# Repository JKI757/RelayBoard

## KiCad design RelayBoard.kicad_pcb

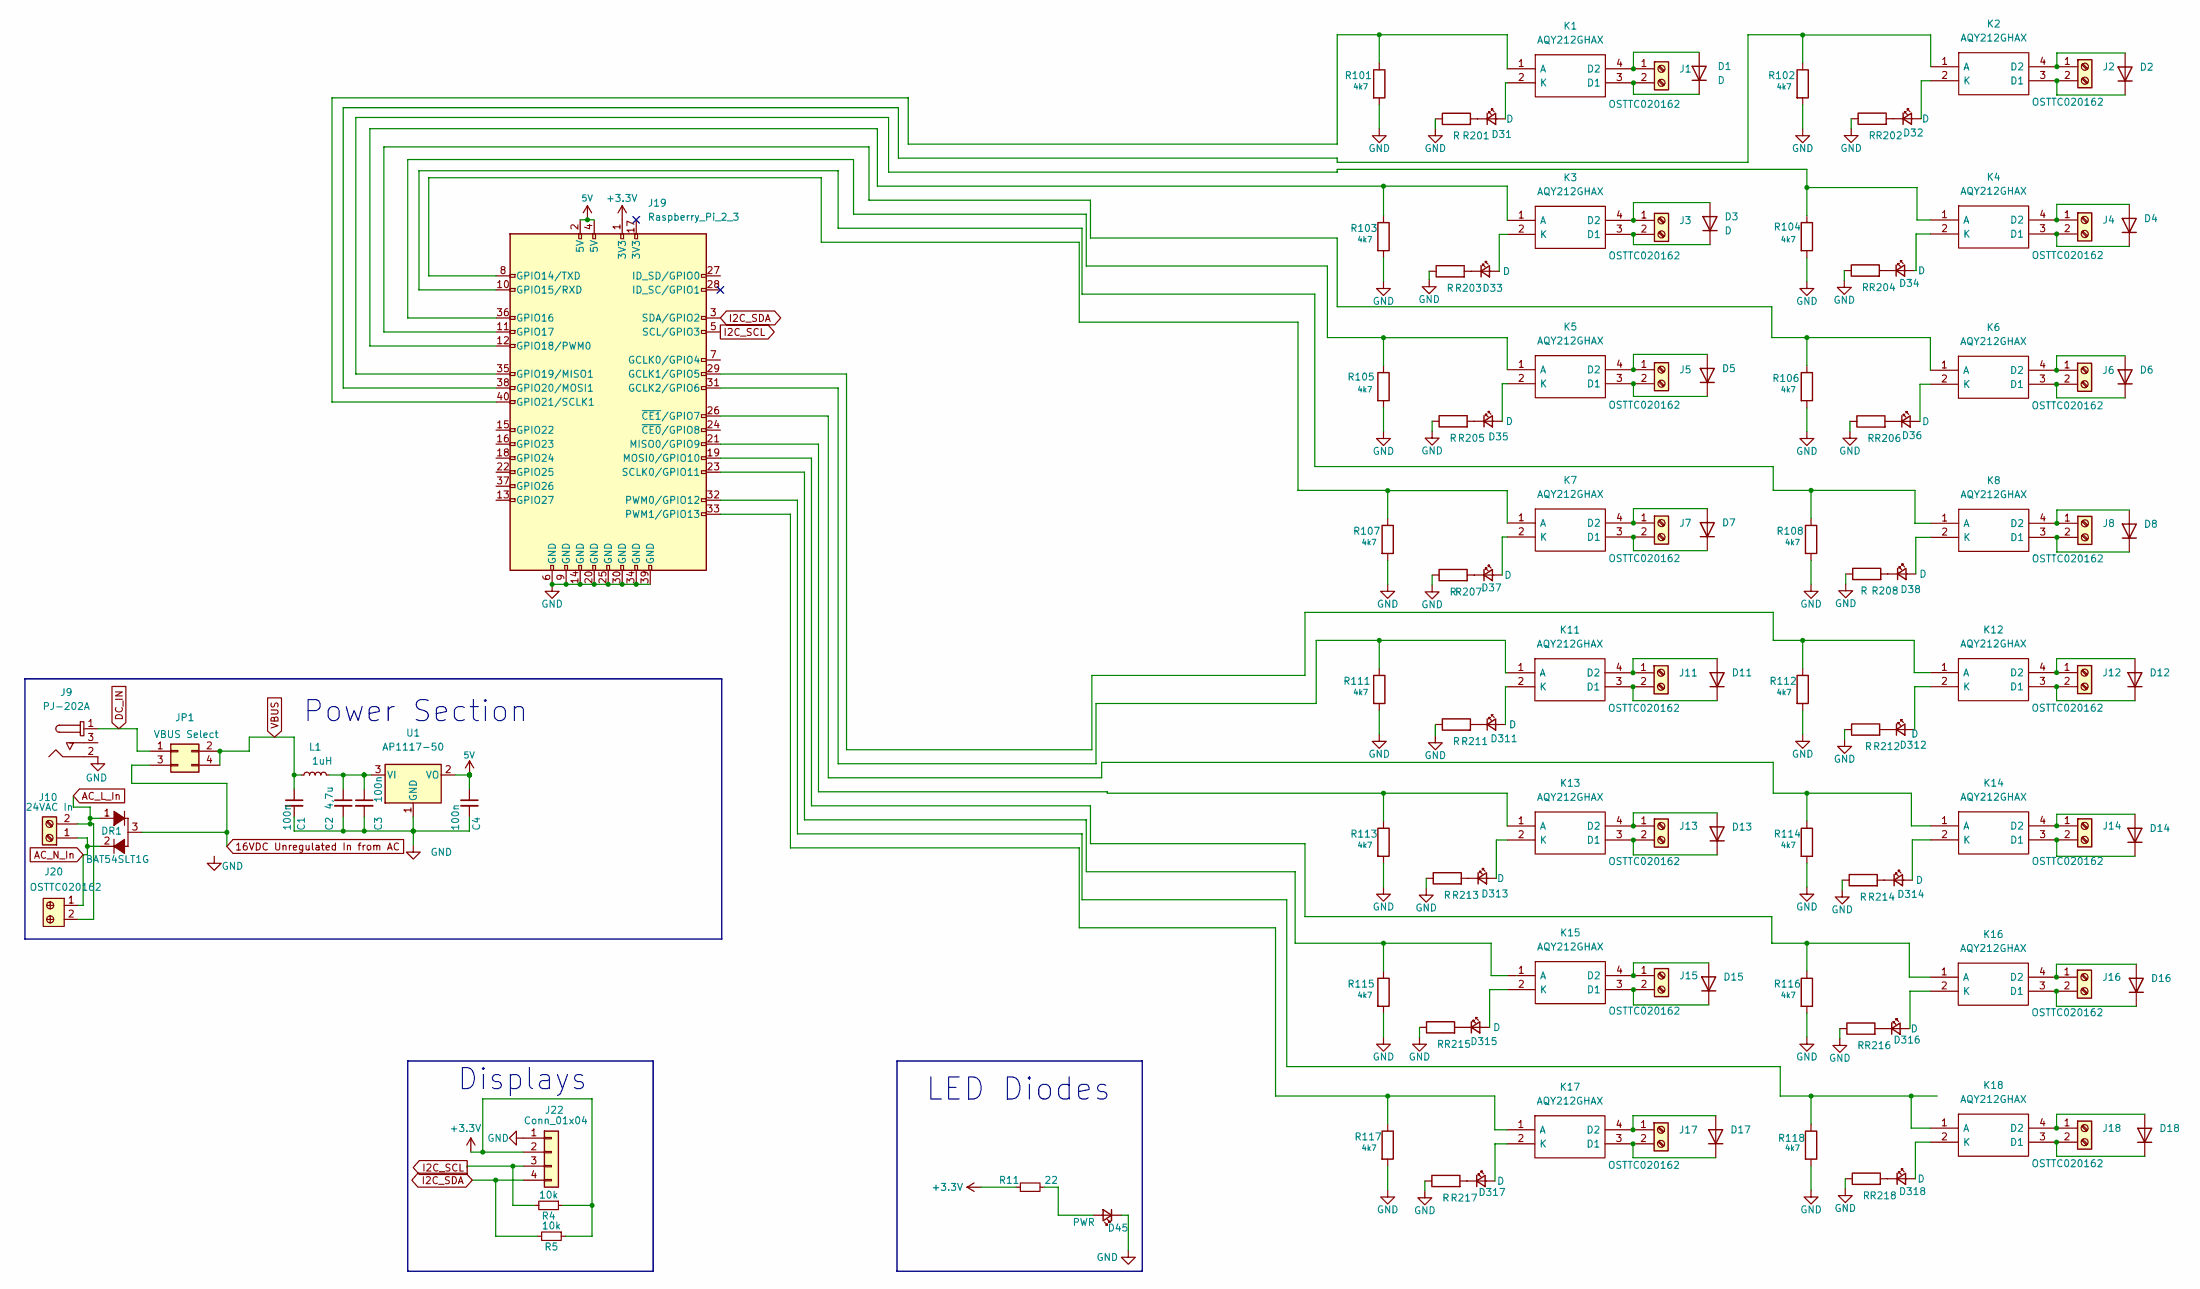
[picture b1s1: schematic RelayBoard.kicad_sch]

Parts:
C1: 100n; C_0805_2012Metric
C2: 4,7u; C_1206_3216Metric
C3: 100n; C_1206_3216Metric
C4: 100n; C_0603_1608Metric
D1, D3: D; D_0805_2012Metric
D2, D4, D5, D6, D7, D8, D11, D12, D13, D14, D15, D16, D17, D18: (no value)
D31, D32, D33, D34, D35, D36, D37, D38, D311, D312, D313, D314, D315, D316, D317, D318: D; LED_0805_2012Metric
D45: PWR; LED_0805_2012Metric
DR1: BAT54SLT1G; SOT-23-3; MPN BAT54SLT1G; Digi-Key_PN BAT54SLT1GOSCT-ND
J1, J2, J3, J4, J5, J6, J7, J8, J11, J12, J13, J14, J15, J16, J17, J18: OSTTC020162; Term_Block_1x2_P5mm
J9: PJ-202A; Barrel_Jack_5.5mmODx2.1mmID_PJ-202A; MPN PJ-202A; Digi-Key_PN CP-202A-ND
J10: 24VAC In; Term_Block_1x2_P5mm
J19: Raspberry_Pi_2_3; PinHeader_2x20_P2.54mm_Vertical
J20: OSTTC020162; Term_Block_1x2_P5mm; MPN OSTTC020162; Digi-Key_PN ED2600-ND
J22: Conn_01x04; PinSocket_1x04_P2.54mm_Vertical
JP1: VBUS Select; PinHeader_2x02_P2.54mm_Vertical
K1, K2, K3, K4, K5, K6, K7, K8, K11, K12, K13, K14, K15, K16, K17, K18: AQY212GHAX; SOP254P962X315-4N; Mouser Part Number 667-AQY212GHAX
L1: 1uH; L_0805_2012Metric
R4, R5: 10k; R_0805_2012Metric
R11: 22; R_0805_2012Metric
R101, R102, R103, R104, R105, R106, R107, R108, R111, R112, R113, R114, R115, R116, R117, R118: 4k7; R_0805_2012Metric
R201, R202, R203, R204, R205, R206, R207, R208, R211, R212, R213, R214, R215, R216, R217, R218: R; R_0805_2012Metric
U1: AP1117-50; SOT-223-3_TabPin2

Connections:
5V: C4.1, J19.2 (5V), J19.4 (5V), U1.2 (VO)
16VDC Unregulated In from AC: DR1.3, JP1.3
+3V3: J19.1 (3V3), J22.2, R4.1, R5.1, R11.1
AC_L_In: DR1.1, J10.2, J20.2
AC_N_In: DR1.2, J10.1, J20.1
DC_IN: J9.1, JP1.1
GND: C1.2, C2.2, C3.2, C4.2, D45.1 (K), J9.2, J19.6 (GND), J19.9 (GND), J19.14 (GND), J19.20 (GND), J19.25 (GND), J19.30 (GND), J19.34 (GND), J19.39 (GND), J22.1, R101.2, R102.2, R103.2, R104.2, R105.2, R106.2, R107.2, R108.2, R111.2, R112.2, R113.2, R114.2, R115.2, R116.2, R117.2, R118.2, R201.1, R202.1, R203.1, R204.1, R205.1, R206.1, R207.1, R208.1, R211.1, R212.1, R213.1, R214.1, R215.1, R216.1, R217.1, R218.1, U1.1 (GND)
I2C_SCL: J19.5 (SCL/GPIO3), J22.3, R4.2
I2C_SDA: J19.3 (SDA/GPIO2), J22.4, R5.2
unnamed: C2.1, C3.1, L1.2, U1.3 (VI)
unnamed: D1.1 (K), J1.2, K1.3 (D1)
unnamed: D1.2 (A), J1.1, K1.4 (D2)
unnamed: D3.1 (K), J3.2, K3.3 (D1)
unnamed: D3.2 (A), J3.1, K3.4 (D2)
unnamed: D7.1 (K), J7.2, K7.3 (D1)
unnamed: D7.2 (A), J7.1, K7.4 (D2)
unnamed: D8.1 (K), J8.2, K8.3 (D1)
unnamed: D14.2 (A), J14.1, K14.4 (D2)
unnamed: D18.1 (K), J18.2, K18.3 (D1)
unnamed: D31.1 (K), R201.2
unnamed: D31.2 (A), K1.2 (K)
unnamed: D32.1 (K), R202.2
unnamed: D32.2 (A), K2.2 (K)
unnamed: D33.1 (K), R203.2
unnamed: D33.2 (A), K3.2 (K)
unnamed: D34.1 (K), R204.2
unnamed: D34.2 (A), K4.2 (K)
unnamed: D35.1 (K), R205.2
unnamed: D35.2 (A), K5.2 (K)
unnamed: D36.1 (K), R206.2
unnamed: D36.2 (A), K6.2 (K)
unnamed: D37.1 (K), R207.2
unnamed: D37.2 (A), K7.2 (K)
unnamed: D38.1 (K), R208.2
unnamed: D38.2 (A), K8.2 (K)
unnamed: D45.2 (A), R11.2
unnamed: D311.1 (K), R211.2
unnamed: D311.2 (A), K11.2 (K)
unnamed: D312.1 (K), R212.2
unnamed: D312.2 (A), K12.2 (K)
unnamed: D313.1 (K), R213.2
unnamed: D313.2 (A), K13.2 (K)
unnamed: D314.1 (K), R214.2
unnamed: D314.2 (A), K14.2 (K)
unnamed: D315.1 (K), R215.2
unnamed: D315.2 (A), K15.2 (K)
unnamed: D316.1 (K), R216.2
unnamed: D316.2 (A), K16.2 (K)
unnamed: D317.1 (K), R217.2
unnamed: D317.2 (A), K17.2 (K)
unnamed: D318.1 (K), R218.2
unnamed: D318.2 (A), K18.2 (K)
unnamed: D2.2 (A), J2.1, K2.4 (D2)
unnamed: D2.1 (K), J2.2, K2.3 (D1)
unnamed: D4.2 (A), J4.1, K4.4 (D2)
unnamed: D4.1 (K), J4.2, K4.3 (D1)
unnamed: D5.2 (A), J5.1, K5.4 (D2)
unnamed: D5.1 (K), J5.2, K5.3 (D1)
unnamed: D6.2 (A), J6.1, K6.4 (D2)
unnamed: D6.1 (K), J6.2, K6.3 (D1)
unnamed: D8.2 (A), J8.1, K8.4 (D2)
unnamed: D11.2 (A), J11.1, K11.4 (D2)
unnamed: D11.1 (K), J11.2, K11.3 (D1)
unnamed: D12.2 (A), J12.1, K12.4 (D2)
unnamed: D12.1 (K), J12.2, K12.3 (D1)
unnamed: D13.2 (A), J13.1, K13.4 (D2)
unnamed: D13.1 (K), J13.2, K13.3 (D1)
unnamed: D14.1 (K), J14.2, K14.3 (D1)
unnamed: D15.2 (A), J15.1, K15.4 (D2)
unnamed: D15.1 (K), J15.2, K15.3 (D1)
unnamed: D16.2 (A), J16.1, K16.4 (D2)
unnamed: D16.1 (K), J16.2, K16.3 (D1)
unnamed: D17.2 (A), J17.1, K17.4 (D2)
unnamed: D17.1 (K), J17.2, K17.3 (D1)
unnamed: D18.2 (A), J18.1, K18.4 (D2)
unnamed: J19.8 (GPIO14/TXD), K7.1 (A), R107.1
unnamed: J19.10 (GPIO15/RXD), K8.1 (A), R108.1
unnamed: J19.11 (GPIO17), K6.1 (A), R106.1
unnamed: J19.12 (GPIO18/PWM0), K3.1 (A), R103.1
unnamed: J19.19 (MOSI0/GPIO10), K16.1 (A), R116.1
unnamed: J19.21 (MISO0/GPIO9), K13.1 (A), R113.1
unnamed: J19.23 (SCLK0/GPIO11), K15.1 (A), R115.1
unnamed: J19.26 (~CE1/GPIO7), K14.1 (A), R114.1
unnamed: J19.29 (GCLK1/GPIO5), K12.1 (A), R112.1
unnamed: J19.31 (GCLK2/GPIO6), K11.1 (A), R111.1
unnamed: J19.32 (PWM0/GPIO12), K18.1 (A), R118.1
unnamed: J19.33 (PWM1/GPIO13), K17.1 (A), R117.1
unnamed: J19.35 (GPIO19/MISO1), K4.1 (A), R104.1
unnamed: J19.36 (GPIO16), K5.1 (A), R105.1
unnamed: J19.38 (GPIO20/MOSI1), K2.1 (A), R102.1
unnamed: J19.40 (GPIO21/SCLK1), K1.1 (A), R101.1
VBUS: C1.1, JP1.2, JP1.4, L1.1

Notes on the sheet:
Power Section
Displays
LED Diodes

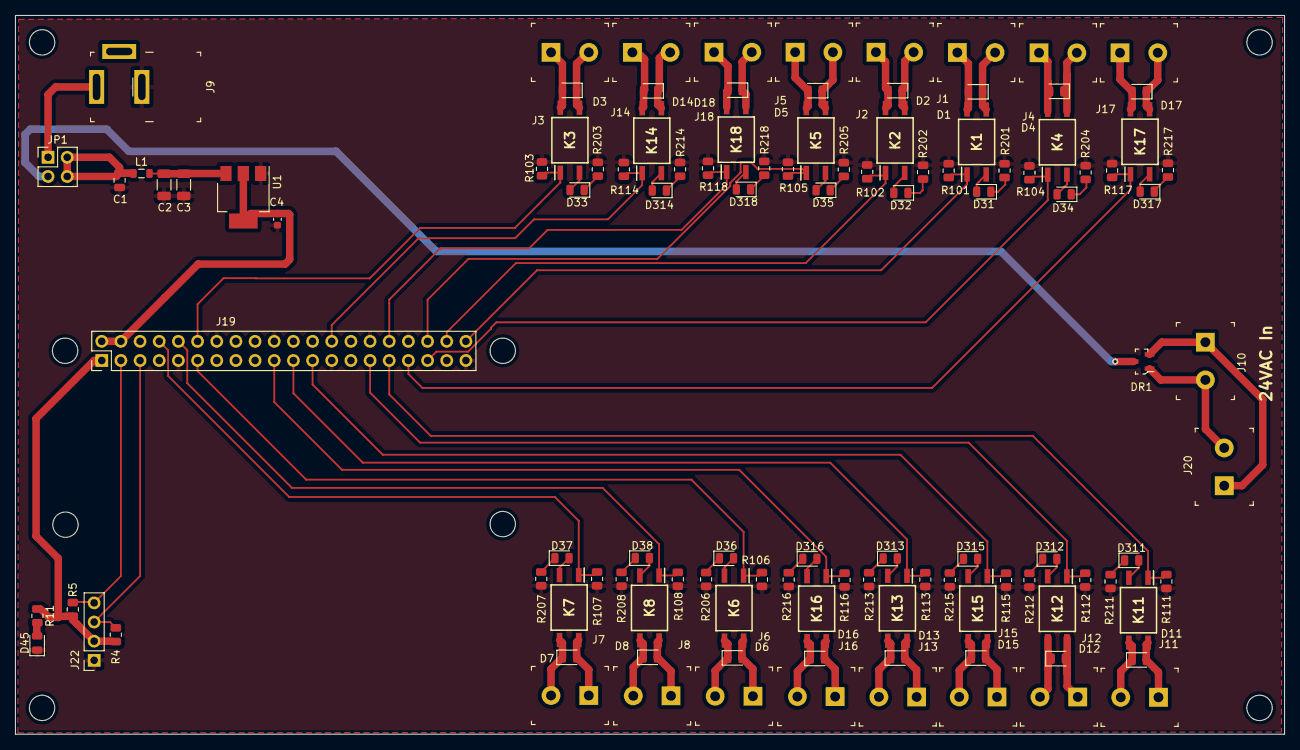
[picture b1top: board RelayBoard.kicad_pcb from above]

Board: 2 copper layers, 168.2 x 95.2 mm, 113 parts (0 on the bottom side), 92 nets.

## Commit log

2022-05-01 first commit with inductive relays
2022-05-02 basic design with solid state relays complete
2022-05-07 remove esp32 and add Raspberry PI, along with AC power suppply
2022-05-07 add gitignore
2022-05-07 fix gitignore and remove backup zips
2022-05-07 replace connectors, reroute GPIOs and power
2022-05-07 fix DRC errors, passes all tests
2022-05-07 final touches
2022-05-08 fix RPI connector orientation
2022-05-08 drc run after connector fix
2022-05-30 total rewrite, solid state relays & change all footprints to 0805s
2022-05-30 fix drc errors, change bottom zone to GND
2022-05-30 resize board
